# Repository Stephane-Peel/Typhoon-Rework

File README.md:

# Typhoon
Clouds variant

Fork to share production files used to make mine.

- Frontpanel rework to my taste.
- Kicad conversion from Diptrace
- 3D CAD : Fusion 360 & STL
- Original Fuzzy BOM reference completed

Beware : 
--------
The current files where used for my build.
It should be ok, but please double check everything to make your own module ;)

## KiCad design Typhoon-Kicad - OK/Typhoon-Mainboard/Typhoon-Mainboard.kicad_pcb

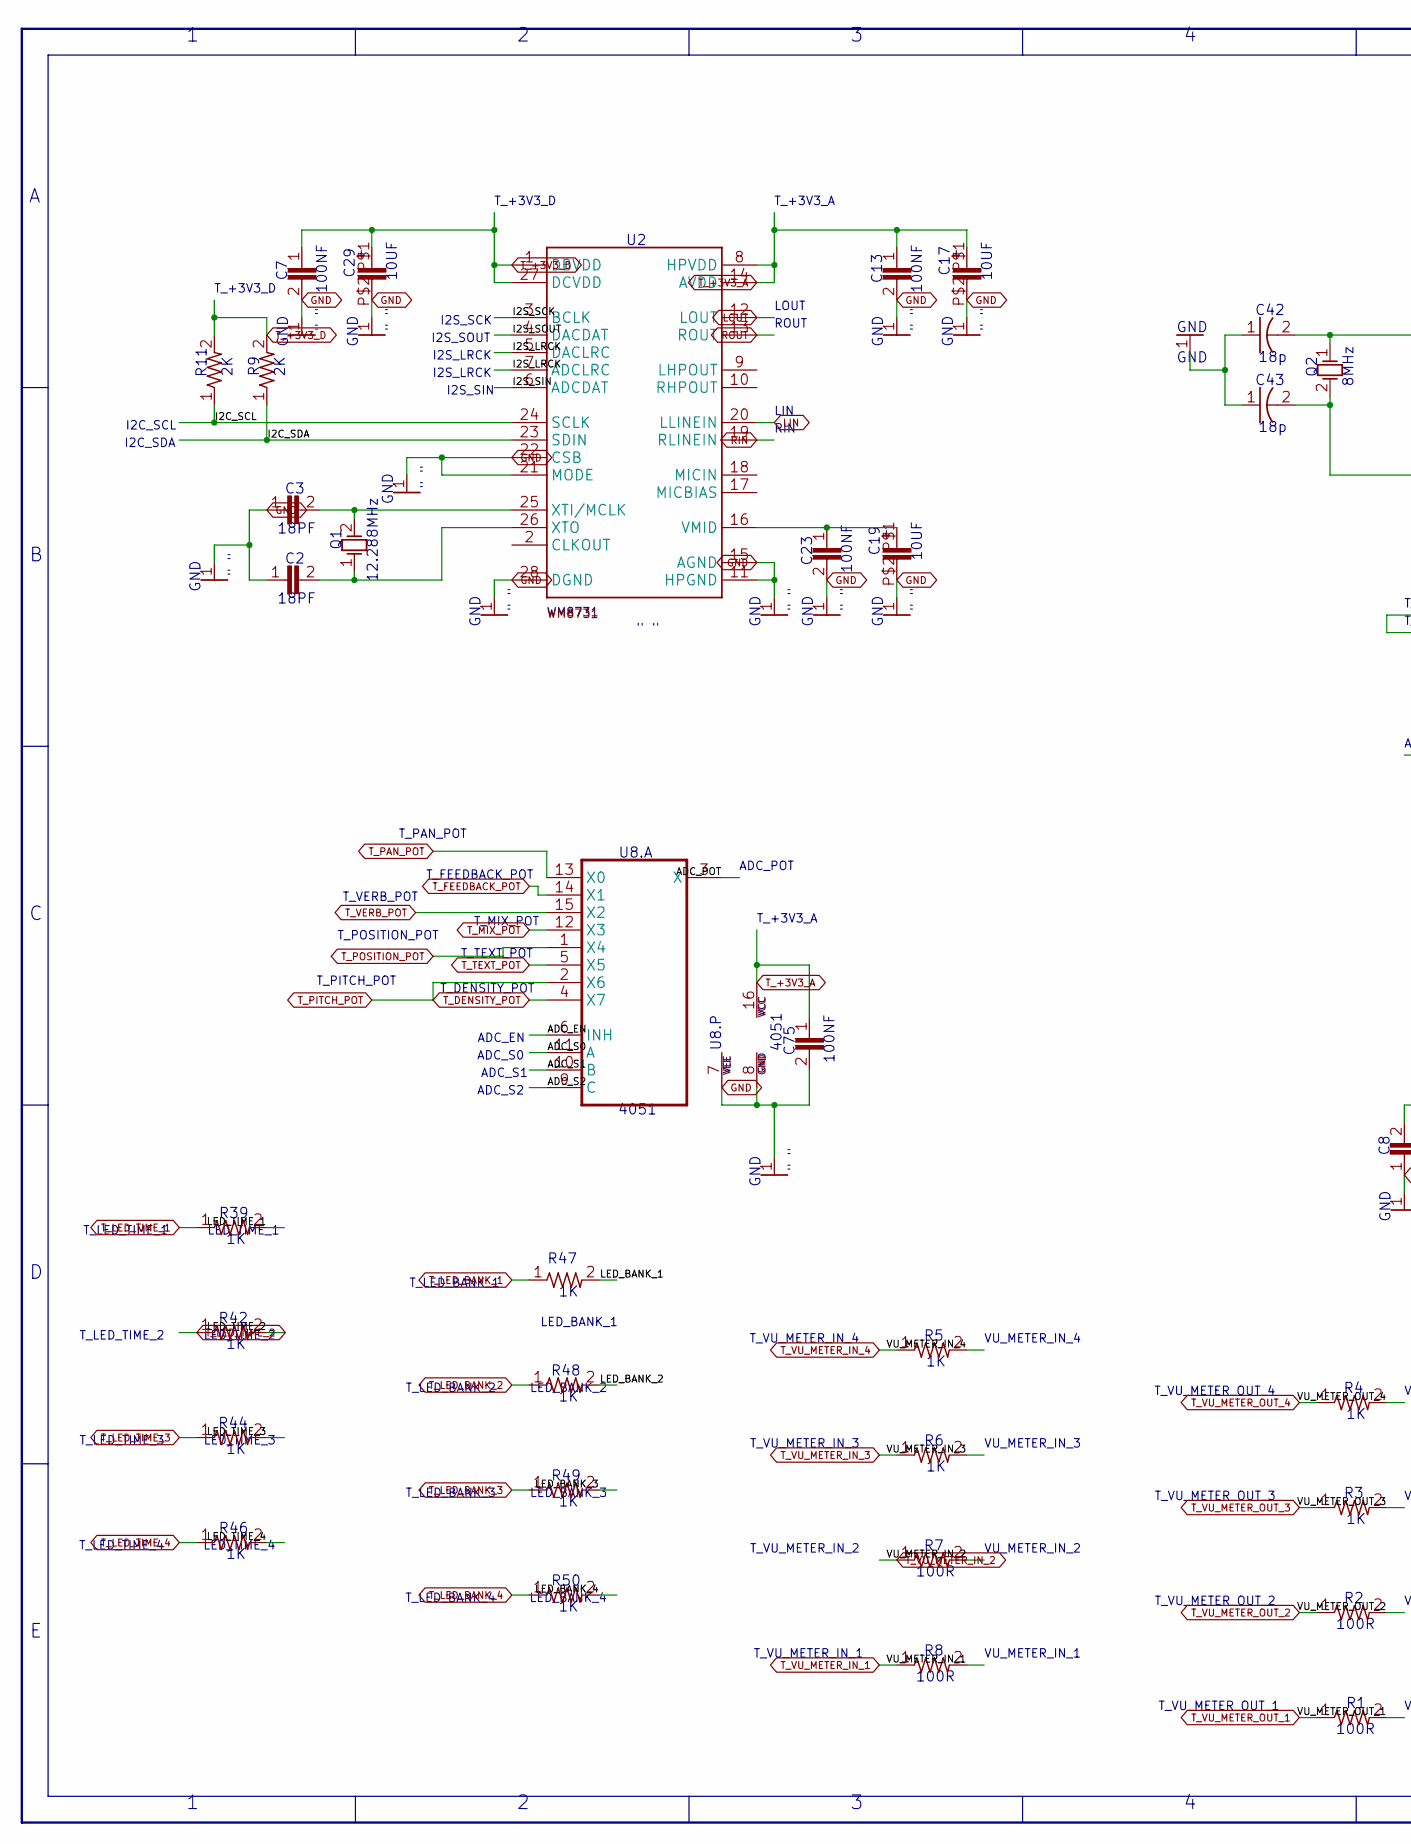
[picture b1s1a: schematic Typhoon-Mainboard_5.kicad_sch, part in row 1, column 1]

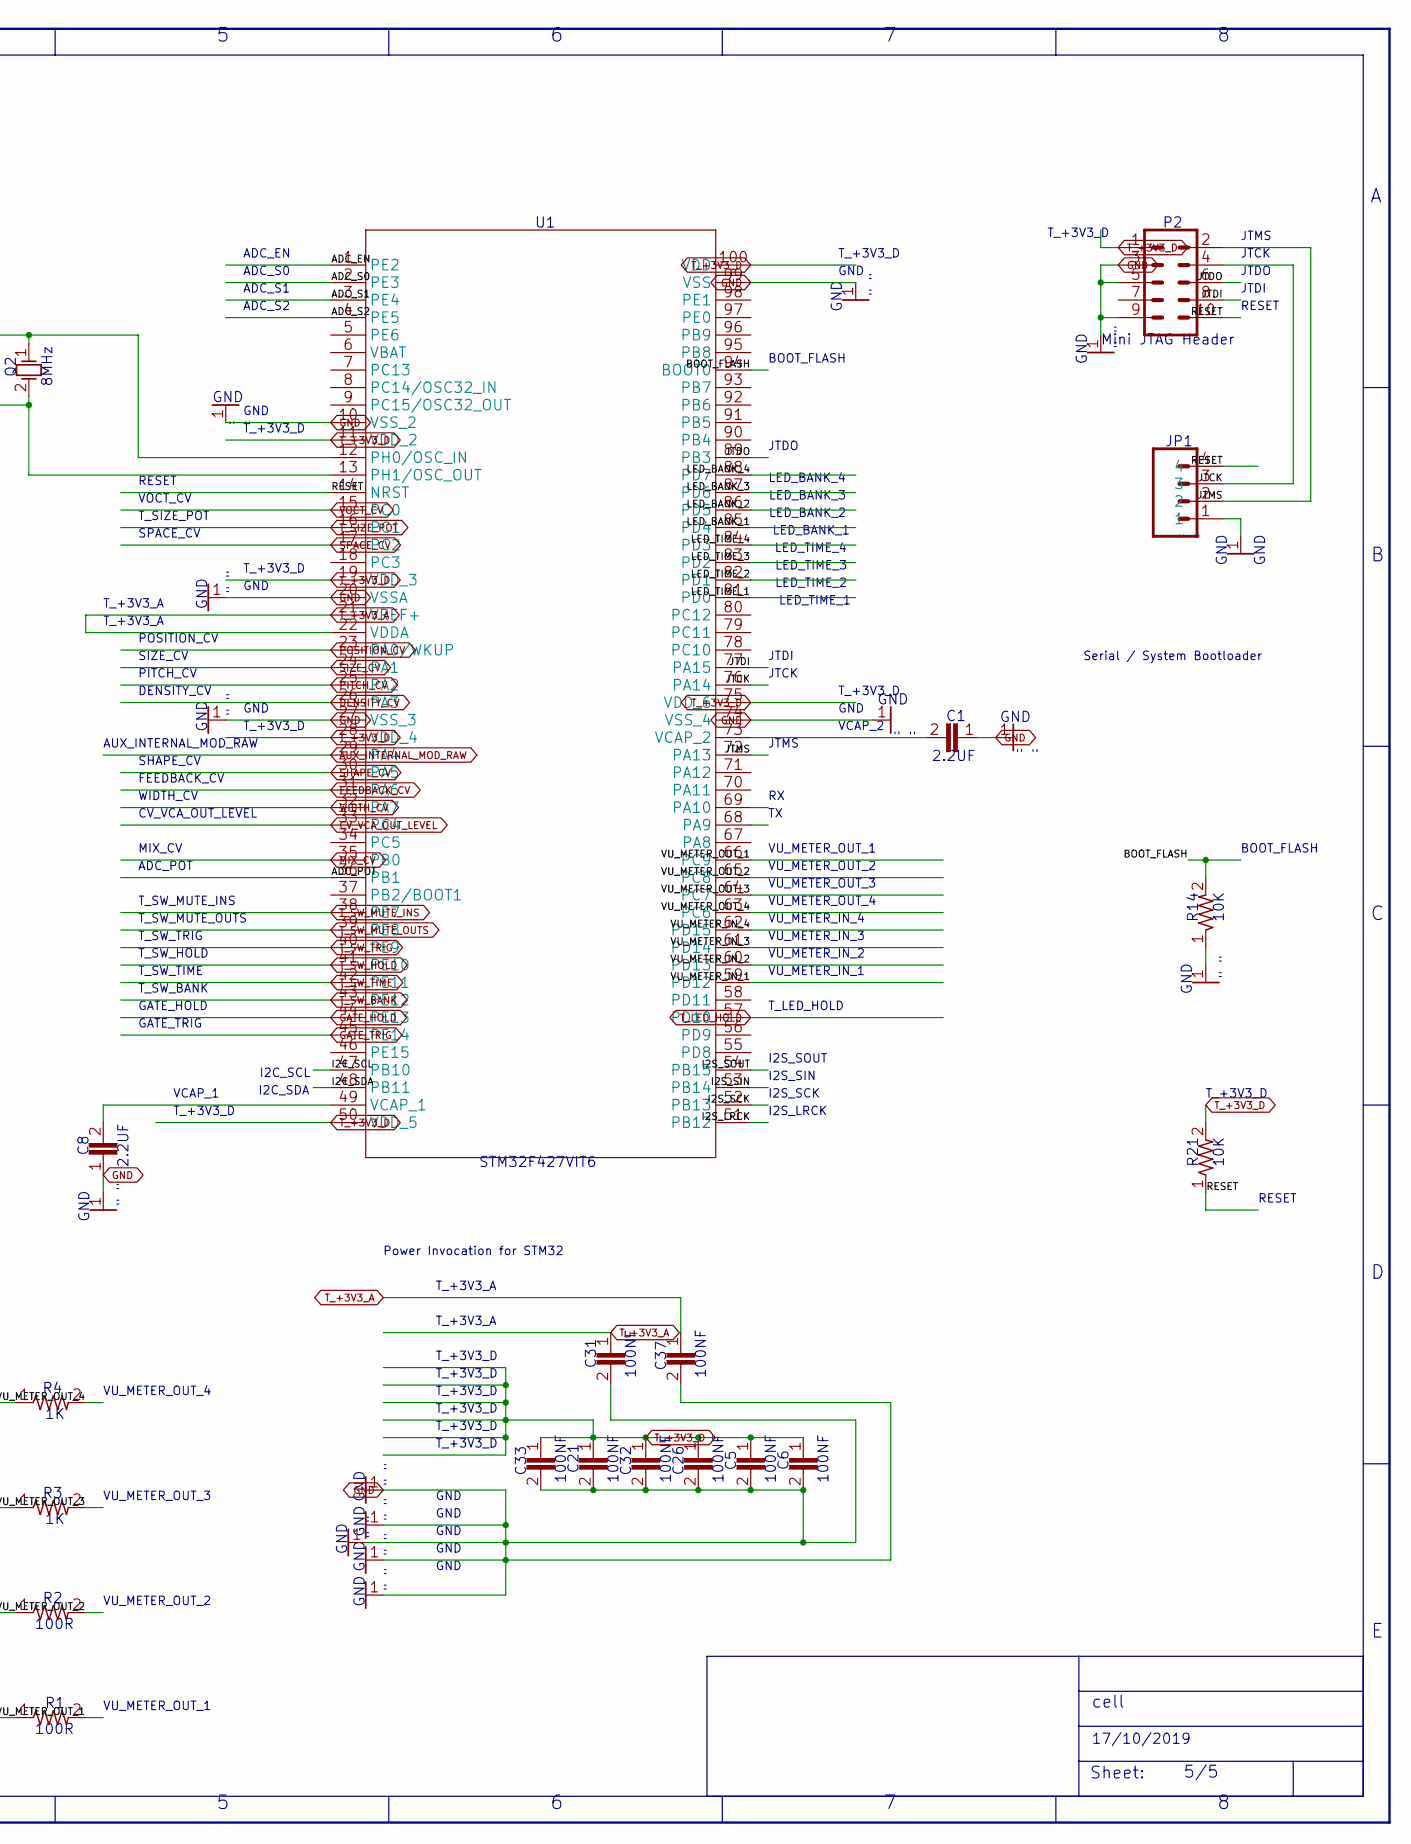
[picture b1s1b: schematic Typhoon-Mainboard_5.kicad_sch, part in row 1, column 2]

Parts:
C1, C8: 2.2UF; CAP_0603
C2, C3: 18PF; CAP_0603
C5, C6, C7, C13, C21, C23, C26, C31, C32, C33, C37, C75: 100NF; CAP_0603
C17, C19, C29: 10UF; EC-4X7
C42, C43: 18p; CAP_0603
JP1: M04PTH; 1X04
P2: Mini JTAG Header; 2X5-1.27
Q1: 12.288MHz; TSC_7A_CRYSTAL
Q2: 8MHz; TSC_7A_CRYSTAL
R1, R2, R7, R8: 100R; RES_0603
R3, R4, R5, R6, R39, R42, R44, R46, R47, R48, R49, R50: 1K; RES_0603
R9, R11: 2K; RES_0603
R14, R21: 10K; RES_0603
U1: STM32F427VIT6; LQFP100-14X14MM
U2: WM8731; SSOP-28
U8: 4051; SO-16

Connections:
ADC_EN: U1.1 (PE2), U8.6 (INH)
ADC_POT: U1.36 (PB1), U8.3 (X)
ADC_S0: U1.2 (PE3), U8.11 (A)
ADC_S1: U1.3 (PE4), U8.10 (B)
ADC_S2: U1.4 (PE5), U8.9 (C)
AUX_INTERNAL_MOD_RAW: U1.29 (PA4); also elsewhere on the board
BOOT_FLASH: R14.2, U1.94 (BOOT0)
CV_VCA_OUT_LEVEL: U1.33 (PC4); also elsewhere on the board
DENSITY_CV: U1.26 (PA3); also elsewhere on the board
FEEDBACK_CV: U1.31 (PA6); also elsewhere on the board
GATE_HOLD: U1.44 (PE13); also elsewhere on the board
GATE_TRIG: U1.45 (PE14); also elsewhere on the board
I2C_SCL: R11.1, U1.47 (PB10), U2.24 (SCLK)
I2C_SDA: R9.1, U1.48 (PB11), U2.23 (SDIN)
I2S_LRCK: U1.51 (PB12), U2.5 (DACLRC), U2.7 (ADCLRC)
I2S_SCK: U1.52 (PB13), U2.3 (BCLK)
I2S_SIN: U1.53 (PB14), U2.6 (ADCDAT)
I2S_SOUT: U1.54 (PB15), U2.4 (DACDAT)
JTCK: JP1.3, P2.4, U1.76 (PA14)
JTDI: P2.8, U1.77 (PA15)
JTDO: P2.6, U1.89 (PB3)
JTMS: JP1.2, P2.2, U1.72 (PA13)
LED_BANK_1: R47.2, U1.85 (PD4)
LED_BANK_2: R48.2, U1.86 (PD5)
LED_BANK_3: R49.2, U1.87 (PD6)
LED_BANK_4: R50.2, U1.88 (PD7)
LED_TIME_1: R39.2, U1.81 (PD0)
LED_TIME_2: R42.2, U1.82 (PD1)
LED_TIME_3: R44.2, U1.83 (PD2)
LED_TIME_4: R46.2, U1.84 (PD3)
LIN: U2.20 (LLINEIN); also elsewhere on the board
LOUT: U2.12 (LOUT); also elsewhere on the board
MIX_CV: U1.35 (PB0); also elsewhere on the board
unnamed: C19.P$1 (POS), C23.1, U2.16 (VMID)
unnamed: C2.2, Q1.1 (OSC1), U2.26 (XTO)
unnamed: C3.2, Q1.2 (OSC2), U2.25 (XTI/MCLK)
unnamed: C42.2, Q2.1 (OSC1), U1.12 (PH0/OSC_IN)
Net_84: C43.2, Q2.2 (OSC2), U1.13 (PH1/OSC_OUT)
PITCH_CV: U1.25 (PA2); also elsewhere on the board
POSITION_CV: U1.23 (PA0/WKUP); also elsewhere on the board
RESET: JP1.4, P2.10, R21.1, U1.14 (NRST)
RIN: U2.19 (RLINEIN); also elsewhere on the board
ROUT: U2.13 (ROUT); also elsewhere on the board
SHAPE_CV: U1.30 (PA5); also elsewhere on the board
SIZE_CV: U1.24 (PA1); also elsewhere on the board
SPACE_CV: U1.17 (PC2); also elsewhere on the board
T_+3V3_A: C13.1, C17.P$1 (POS), C31.1, C37.1, C75.1, U1.21 (VREF+), U1.22 (VDDA), U2.8 (HPVDD), U2.14 (AVDD), U8.16 (VCC); also elsewhere on the board
T_DENSITY_POT: U8.4 (X7); also elsewhere on the board
T_FEEDBACK_POT: U8.14 (X1); also elsewhere on the board
T_LED_BANK_1: R47.1; also elsewhere on the board
T_LED_BANK_2: R48.1; also elsewhere on the board
T_LED_BANK_3: R49.1; also elsewhere on the board
T_LED_BANK_4: R50.1; also elsewhere on the board
T_LED_HOLD: U1.57 (PD10); also elsewhere on the board
T_LED_TIME_1: R39.1; also elsewhere on the board
T_LED_TIME_2: R42.1; also elsewhere on the board
T_LED_TIME_3: R44.1; also elsewhere on the board
T_LED_TIME_4: R46.1; also elsewhere on the board
T_MIX_POT: U8.12 (X3); also elsewhere on the board
T_PAN_POT: U8.13 (X0); also elsewhere on the board
T_PITCH_POT: U8.2 (X6); also elsewhere on the board
T_POSITION_POT: U8.1 (X4); also elsewhere on the board
T_SIZE_POT: U1.16 (PC1); also elsewhere on the board
T_SW_HOLD: U1.41 (PE10); also elsewhere on the board
T_SW_MUTE_OUTS: U1.39 (PE8); also elsewhere on the board
T_SW_TIME: U1.42 (PE11); also elsewhere on the board
T_SW_TRIG: U1.40 (PE9); also elsewhere on the board
T_TEXT_POT: U8.5 (X5); also elsewhere on the board
T_VERB_POT: U8.15 (X2); also elsewhere on the board
T_VU_METER_IN_1: R8.1; also elsewhere on the board
T_VU_METER_IN_2: R7.1; also elsewhere on the board
T_VU_METER_IN_3: R6.1; also elsewhere on the board
T_VU_METER_IN_4: R5.1; also elsewhere on the board
T_VU_METER_OUT_1: R1.1; also elsewhere on the board
T_VU_METER_OUT_2: R2.1; also elsewhere on the board
T_VU_METER_OUT_3: R3.1; also elsewhere on the board
T_VU_METER_OUT_4: R4.1; also elsewhere on the board
VCAP_1: C8.2, U1.49 (VCAP_1)
VCAP_2: C1.2, U1.73 (VCAP_2)
VOCT_CV: U1.15 (PC0); also elsewhere on the board
VU_METER_IN_1: R8.2, U1.59 (PD12)
VU_METER_IN_2: R7.2, U1.60 (PD13)
VU_METER_IN_3: R6.2, U1.61 (PD14)
VU_METER_IN_4: R5.2, U1.62 (PD15)
VU_METER_OUT_1: R1.2, U1.66 (PC9)
VU_METER_OUT_2: R2.2, U1.65 (PC8)
VU_METER_OUT_3: R3.2, U1.64 (PC7)
VU_METER_OUT_4: R4.2, U1.63 (PC6)
WIDTH_CV: U1.32 (PA7); also elsewhere on the board

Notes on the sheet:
C13
10K
JTDO
I2S_SOUT
GND
LED_TIME_1
R14
100NF
VU_METER_OUT_4
LED_BANK_2
JTMS
T_VU_METER_OUT_2
" "
T_+3V3_D
12.288MHz
18PF
WM8731
T_SW_TRIG
BOOT_FLASH
CV_VCA_OUT_LEVEL
100R
T_LED_TIME_2
T_+3V3_A
U8.A
ADC_S2
LED_BANK_4
LED_TIME_4
ROUT
JTCK
LED_TIME_2
LED_BANK_3
T_LED_TIME_1
C75
JTDI
T_SW_MUTE_INS
C42
VU_METER_OUT_2
I2S_LRCK
LED_BANK_1
I2C_SCL

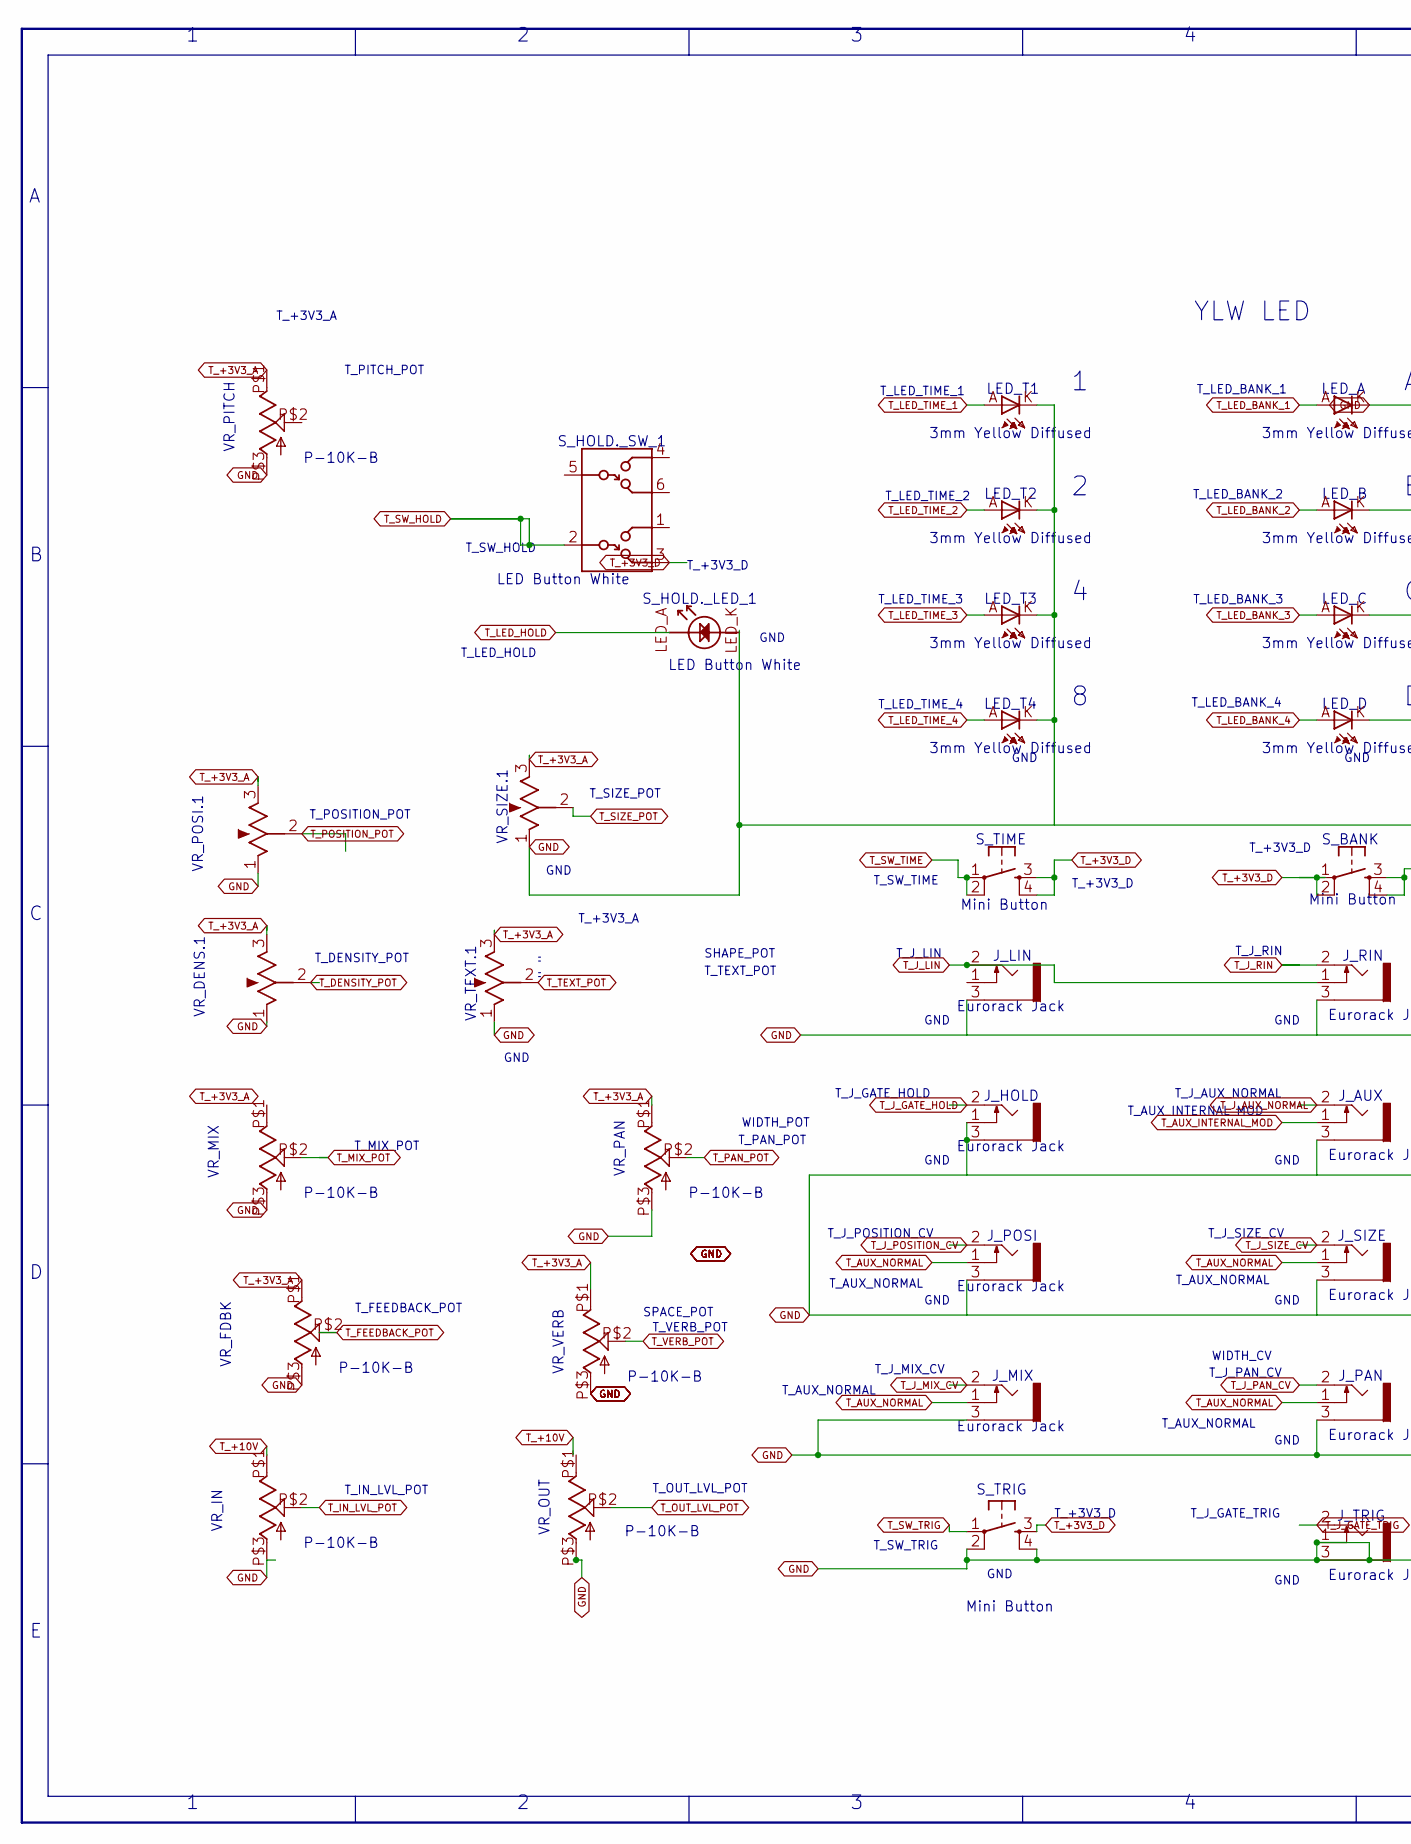
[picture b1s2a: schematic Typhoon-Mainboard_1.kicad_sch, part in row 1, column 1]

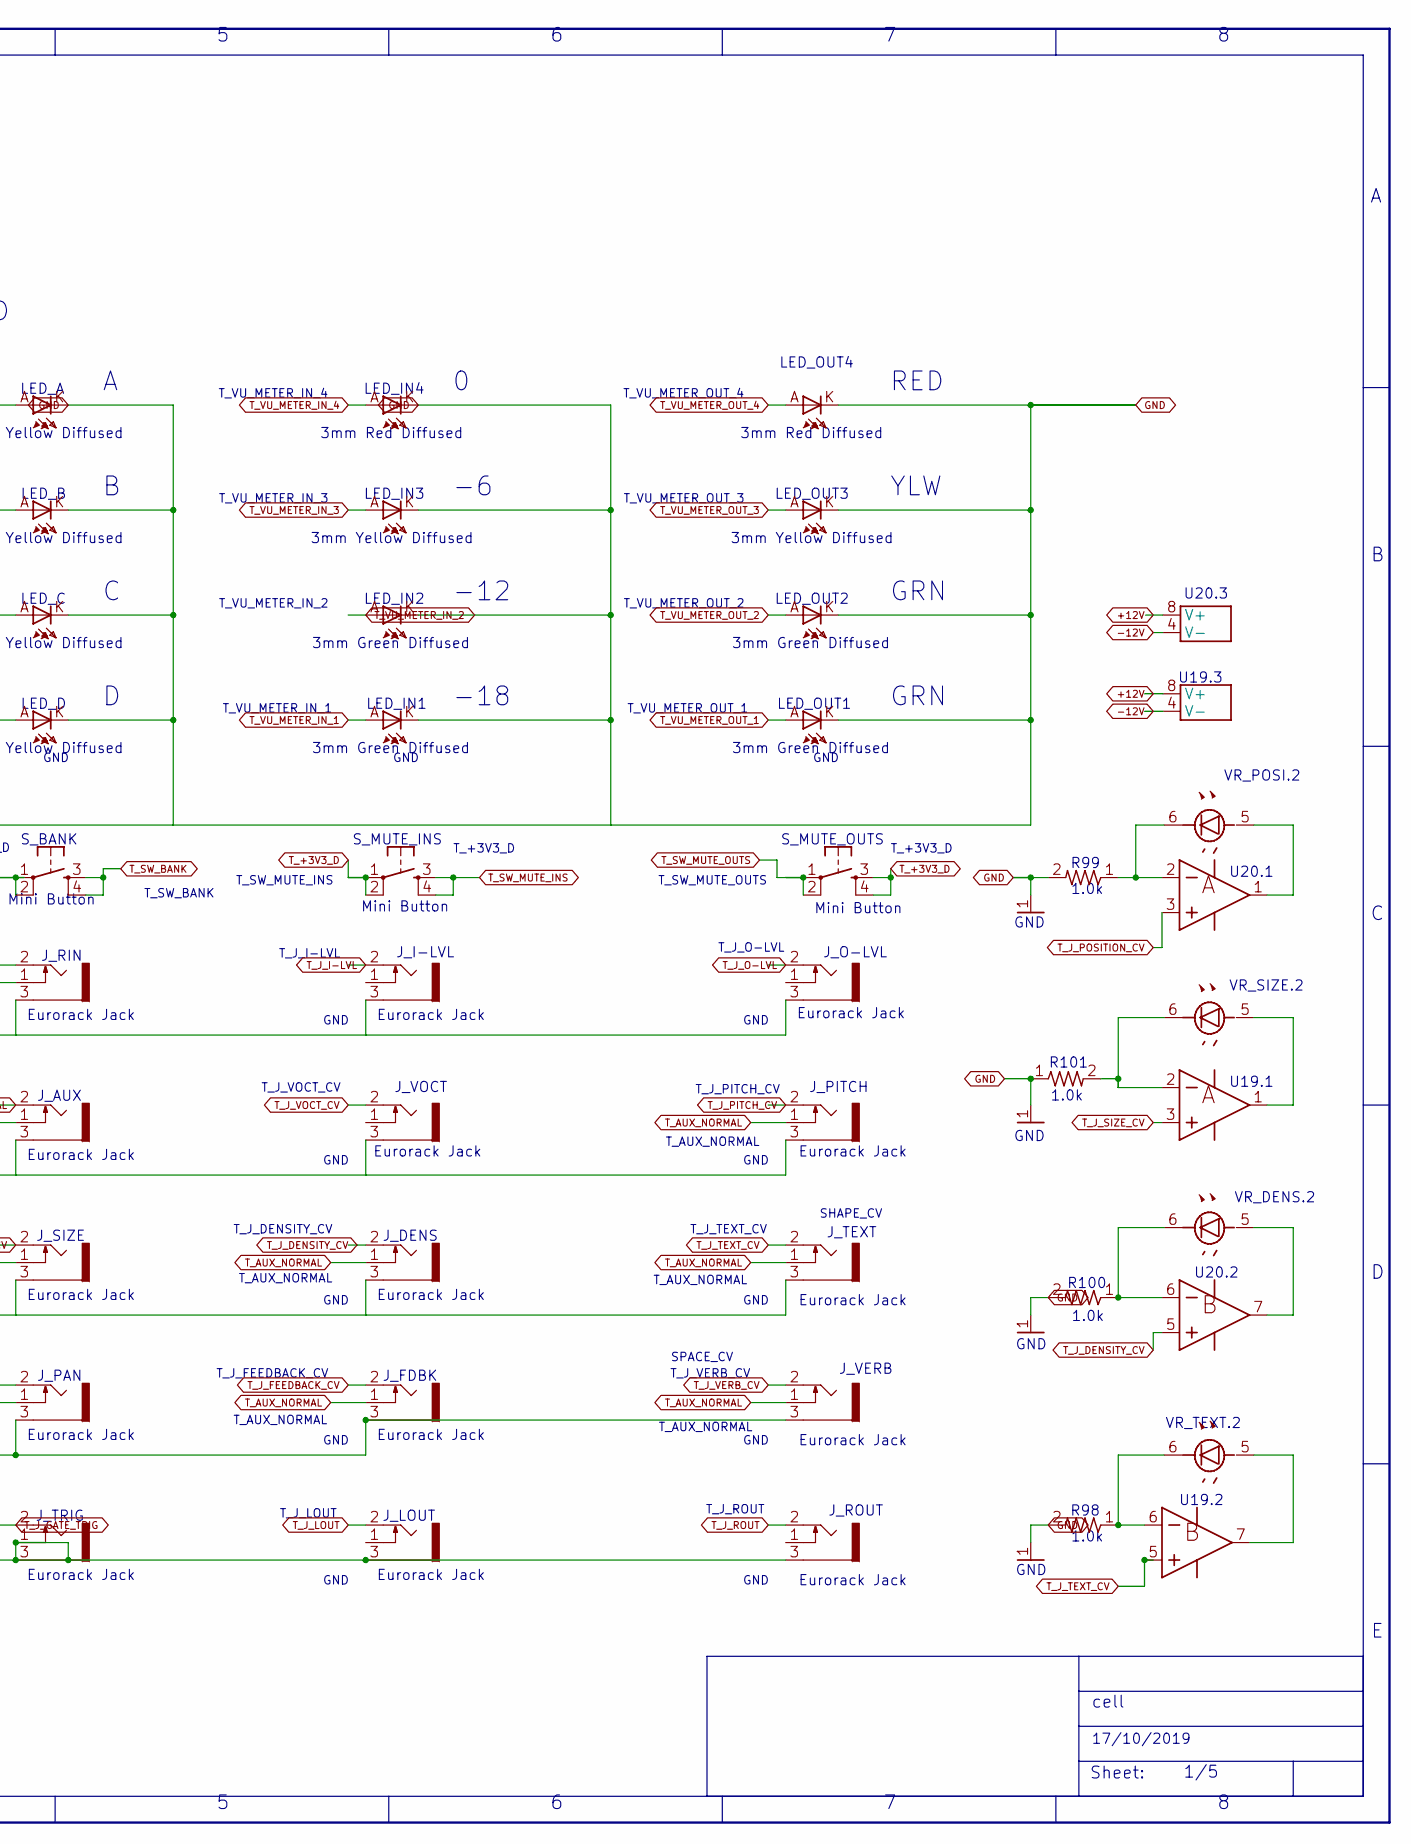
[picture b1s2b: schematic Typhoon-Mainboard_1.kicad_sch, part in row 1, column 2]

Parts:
J_AUX0: Eurorack Jack; THONKICONN
J_DENS0: Eurorack Jack; THONKICONN
J_FDBK0: Eurorack Jack; THONKICONN
J_HOLD0: Eurorack Jack; THONKICONN
J_I-LVL0: Eurorack Jack; THONKICONN
J_LIN0: Eurorack Jack; THONKICONN
J_LOUT0: Eurorack Jack; THONKICONN
J_MIX0: Eurorack Jack; THONKICONN
J_O-LVL0: Eurorack Jack; THONKICONN
J_PAN0: Eurorack Jack; THONKICONN
J_PITCH0: Eurorack Jack; THONKICONN
J_POSI0: Eurorack Jack; THONKICONN
J_RIN0: Eurorack Jack; THONKICONN
J_ROUT0: Eurorack Jack; THONKICONN
J_SIZE0: Eurorack Jack; THONKICONN
J_TEXT0: Eurorack Jack; THONKICONN
J_TRIG0: Eurorack Jack; THONKICONN
J_VERB0: Eurorack Jack; THONKICONN
J_VOCT0: Eurorack Jack; THONKICONN
LED_A0: 3mm Yellow Diffused; LED_SILK
LED_B0: 3mm Yellow Diffused; LED_SILK
LED_C0: 3mm Yellow Diffused; LED_SILK
LED_D0: 3mm Yellow Diffused; LED_SILK
LED_IN1, LED_IN2: 3mm Green Diffused; LED_SILK
LED_IN3: 3mm Yellow Diffused; LED_SILK
LED_IN4: 3mm Red Diffused; LED_SILK
LED_OUT1, LED_OUT2: 3mm Green Diffused; LED_SILK
LED_OUT3: 3mm Yellow Diffused; LED_SILK
LED_OUT4: 3mm Red Diffused; LED_SILK
LED_T1, LED_T2, LED_T3, LED_T4: 3mm Yellow Diffused; LED_SILK
R98, R99, R100, R101: 1.0k; RES_0603
S_BANK0: Mini Button; TACTILE-PTH_SILK
S_HOLD0: LED Button White; LED_BUTTON_SILK
S_MUTE_INS0: Mini Button; TACTILE-PTH_SILK
S_MUTE_OUTS0: Mini Button; TACTILE-PTH_SILK
S_TIME0: Mini Button; TACTILE-PTH_SILK
S_TRIG0: Mini Button; TACTILE-PTH_SILK
U19, U20: TLV2172; TSSOP-8
VR_DENS0: BOURNS_PTL_LED_SLIDE_POT; BOURNS_PTL_30MM
VR_FDBK0: P-10K-B; ALPS_POT_VERTICAL_PS
VR_IN0: P-10K-B; ALPS_POT_VERTICAL_PS
VR_MIX0: P-10K-B; ALPS_POT_VERTICAL_PS
VR_OUT0: P-10K-B; ALPS_POT_VERTICAL_PS
VR_PAN0: P-10K-B; ALPS_POT_VERTICAL_PS
VR_PITCH0: P-10K-B; ALPS_POT_VERTICAL_PS
VR_POSI0: BOURNS_PTL_LED_SLIDE_POT; BOURNS_PTL_30MM
VR_SIZE0: BOURNS_PTL_LED_SLIDE_POT; BOURNS_PTL_30MM
VR_TEXT0: BOURNS_PTL_LED_SLIDE_POT; BOURNS_PTL_30MM
VR_VERB0: P-10K-B; ALPS_POT_VERTICAL_PS

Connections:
+12V: U19.8 (V+), U20.8 (V+); also elsewhere on the board
-12V: U19.4 (V-), U20.4 (V-); also elsewhere on the board
Net_1: R99.1, U20.2 (IN-), VR_POSI0.6 (gnd@2)
Net_110: R100.1, U20.6 (IN-), VR_DENS0.6 (gnd@2)
Net_116: R98.1, U19.6 (IN-), VR_TEXT0.6 (gnd@2)
Net_177: U20.1 (OUT), VR_POSI0.5 (gnd@1)
Net_178: U19.1 (OUT), VR_SIZE0.5 (gnd@1)
Net_182: U20.7 (OUT), VR_DENS0.5 (gnd@1)
Net_183: U19.7 (OUT), VR_TEXT0.5 (gnd@1)
T_+3V3_A: VR_DENS0.3 (CW), VR_FDBK0.P$1 (3), VR_MIX0.P$1 (3), VR_PAN0.P$1 (3), VR_PITCH0.P$1 (3), VR_POSI0.3 (CW), VR_SIZE0.3 (CW), VR_TEXT0.3 (CW), VR_VERB0.P$1 (3); also elsewhere on the board
T_+10V: VR_IN0.P$1 (3), VR_OUT0.P$1 (3); also elsewhere on the board
T_AUX_INTERNAL_MOD: J_AUX0.1 (NORM); also elsewhere on the board
T_AUX_NORMAL: J_DENS0.1 (NORM), J_FDBK0.1 (NORM), J_MIX0.1 (NORM), J_PAN0.1 (NORM), J_PITCH0.1 (NORM), J_POSI0.1 (NORM), J_SIZE0.1 (NORM), J_TEXT0.1 (NORM), J_VERB0.1 (NORM); also elsewhere on the board
T_DENSITY_POT: VR_DENS0.2 (W); also elsewhere on the board
T_FEEDBACK_POT: VR_FDBK0.P$2 (2); also elsewhere on the board
T_IN_LVL_POT: VR_IN0.P$2 (2); also elsewhere on the board
T_J_AUX_NORMAL: J_AUX0.2 (TIP); also elsewhere on the board
T_J_DENSITY_CV: J_DENS0.2 (TIP), U20.5 (IN+); also elsewhere on the board
T_J_FEEDBACK_CV: J_FDBK0.2 (TIP); also elsewhere on the board
T_J_GATE_HOLD: J_HOLD0.2 (TIP); also elsewhere on the board
T_J_GATE_TRIG: J_TRIG0.2 (TIP); also elsewhere on the board
T_J_I-LVL: J_I-LVL0.2 (TIP); also elsewhere on the board
T_J_LIN: J_LIN0.2 (TIP), J_RIN0.1 (NORM); also elsewhere on the board
T_J_LOUT: J_LOUT0.2 (TIP); also elsewhere on the board
T_J_MIX_CV: J_MIX0.2 (TIP); also elsewhere on the board
T_J_O-LVL: J_O-LVL0.2 (TIP); also elsewhere on the board
T_J_PAN_CV: J_PAN0.2 (TIP); also elsewhere on the board
T_J_PITCH_CV: J_PITCH0.2 (TIP); also elsewhere on the board
T_J_POSITION_CV: J_POSI0.2 (TIP), U20.3 (IN+); also elsewhere on the board
T_J_RIN: J_RIN0.2 (TIP); also elsewhere on the board
T_J_ROUT: J_ROUT0.2 (TIP); also elsewhere on the board
T_J_SIZE_CV: J_SIZE0.2 (TIP), U19.3 (IN+); also elsewhere on the board
T_J_TEXT_CV: J_TEXT0.2 (TIP), U19.5 (IN+); also elsewhere on the board
T_J_VERB_CV: J_VERB0.2 (TIP); also elsewhere on the board
T_J_VOCT_CV: J_VOCT0.2 (TIP); also elsewhere on the board
T_LED_BANK_1: LED_A0.A; also elsewhere on the board
T_LED_BANK_2: LED_B0.A; also elsewhere on the board
T_LED_BANK_3: LED_C0.A; also elsewhere on the board
T_LED_BANK_4: LED_D0.A; also elsewhere on the board
T_LED_HOLD: S_HOLD0.LED_A; also elsewhere on the board
T_LED_TIME_1: LED_T1.A; also elsewhere on the board
T_LED_TIME_2: LED_T2.A; also elsewhere on the board
T_LED_TIME_3: LED_T3.A; also elsewhere on the board
T_LED_TIME_4: LED_T4.A; also elsewhere on the board
T_MIX_POT: VR_MIX0.P$2 (2); also elsewhere on the board
T_OUT_LVL_POT: VR_OUT0.P$2 (2); also elsewhere on the board
T_PAN_POT: VR_PAN0.P$2 (2); also elsewhere on the board
T_PITCH_POT: VR_PITCH0.P$2 (2); also elsewhere on the board
T_POSITION_POT: VR_POSI0.2 (W); also elsewhere on the board
T_SIZE_POT: VR_SIZE0.2 (W); also elsewhere on the board
T_SW_HOLD: S_HOLD0.2; also elsewhere on the board
T_SW_MUTE_OUTS: S_MUTE_OUTS0.1, S_MUTE_OUTS0.2; also elsewhere on the board
T_SW_TIME: S_TIME0.1, S_TIME0.2; also elsewhere on the board
T_SW_TRIG: S_TRIG0.1; also elsewhere on the board
T_TEXT_POT: VR_TEXT0.2 (W); also elsewhere on the board
T_VERB_POT: VR_VERB0.P$2 (2); also elsewhere on the board
T_VU_METER_IN_1: LED_IN1.A; also elsewhere on the board
T_VU_METER_IN_2: LED_IN2.A; also elsewhere on the board
T_VU_METER_IN_3: LED_IN3.A; also elsewhere on the board
T_VU_METER_IN_4: LED_IN4.A; also elsewhere on the board
T_VU_METER_OUT_1: LED_OUT1.A; also elsewhere on the board
T_VU_METER_OUT_2: LED_OUT2.A; also elsewhere on the board
T_VU_METER_OUT_3: LED_OUT3.A; also elsewhere on the board
T_VU_METER_OUT_4: LED_OUT4.A; also elsewhere on the board

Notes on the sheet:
T_+3V3_A
GND
S_TIME
T_+3V3_D
Eurorack Jack
VR_TEXT.1
LED_OUT3
LED_IN3
T_J_GATE_TRIG
T_J_VERB_CV
T_VU_METER_IN_4
T_VU_METER_OUT_2
T_IN_LVL_POT
VR_PAN
WIDTH_POT
J_I-LVL
P-10K-B
1.0k
J_LIN
T_PITCH_POT
T_SW_HOLD
T_POSITION_POT
T_SW_TRIG
3mm Yellow Diffused
SHAPE_POT
T_LED_TIME_2
J_TRIG
J_AUX
3mm Red Diffused
S_MUTE_INS
T_SW_MUTE_OUTS
WIDTH_CV
T_J_POSITION_CV
T_AUX_NORMAL
VR_VERB
LED_IN1
Mini Button
LED_OUT2
VR_MIX
J_PITCH

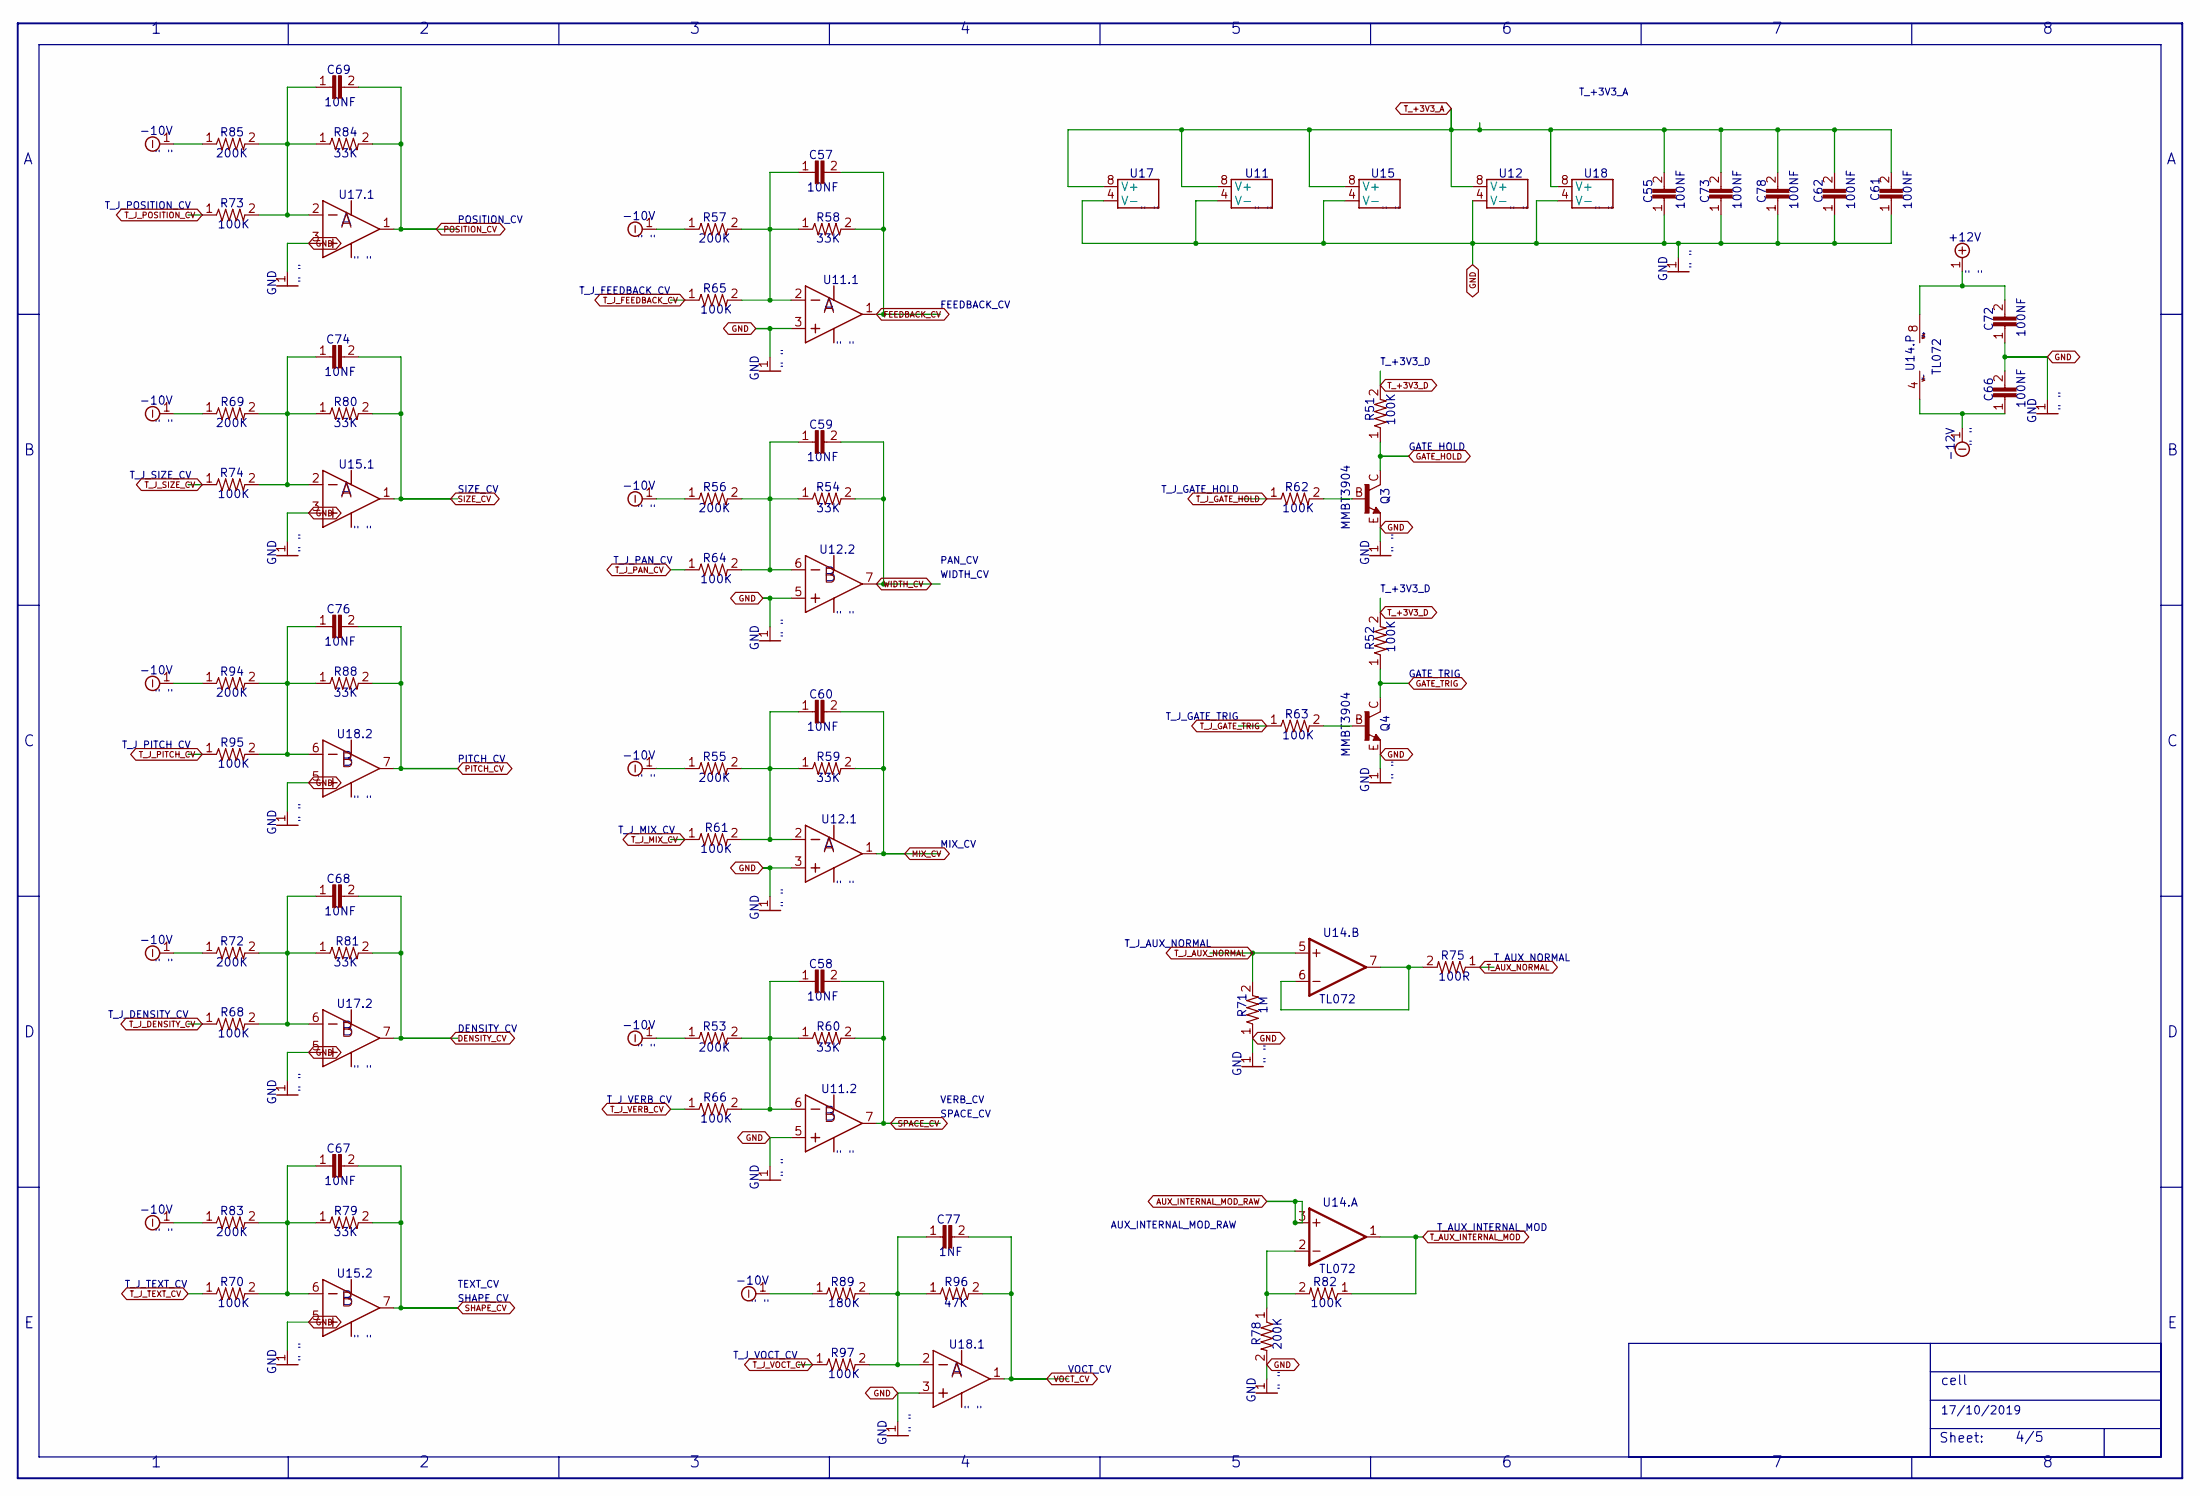
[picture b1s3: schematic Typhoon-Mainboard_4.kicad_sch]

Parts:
C55, C61, C62, C66, C72, C73, C78: 100NF; CAP_0603
C57, C58, C59, C60, C67, C68, C69, C74, C76: 10NF; CAP_0603
C77: 1NF; CAP_0603
Q3, Q4: MMBT3904; SOT23-BEC
R51, R52, R61, R62, R63, R64, R65, R66, R68, R70, R73, R74, R82, R95, R97: 100K; RES_0603
R53, R55, R56, R57, R69, R72, R78, R83, R85, R94: 200K; RES_0603
R54, R58, R59, R60, R79, R80, R81, R84, R88: 33K; RES_0603
R71: 1M; RES_0603
R75: 100R; RES_0603
R89: 180K; RES_0603
R96: 47K; RES_0603
U11, U12, U15, U17, U18: MCP6002; SOIC-8_150MIL
U14: TL072; SO-8

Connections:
+12V: C72.2, U14.8 (V+); also elsewhere on the board
-10V: R53.1, R55.1, R56.1, R57.1, R69.1, R72.1, R83.1, R85.1, R89.1, R94.1; also elsewhere on the board
-12V: C66.1, U14.4 (V-); also elsewhere on the board
AUX_INTERNAL_MOD_RAW: U14.3 (+IN); also elsewhere on the board
DENSITY_CV: C68.2, R81.2, U17.7 (OUT); also elsewhere on the board
FEEDBACK_CV: C57.2, R58.2, U11.1 (OUT); also elsewhere on the board
GATE_HOLD: Q3.C, R51.1; also elsewhere on the board
GATE_TRIG: Q4.C, R52.1; also elsewhere on the board
MIX_CV: C60.2, R59.2, U12.1 (OUT); also elsewhere on the board
unnamed: C74.1, R69.2, R74.2, R80.1, U15.2 (IN-)
unnamed: C76.1, R88.1, R94.2, R95.2, U18.6 (IN-)
unnamed: C68.1, R68.2, R72.2, R81.1, U17.6 (IN-)
unnamed: C57.1, R57.2, R58.1, R65.2, U11.2 (IN-)
unnamed: C59.1, R54.1, R56.2, R64.2, U12.6 (IN-)
unnamed: C60.1, R55.2, R59.1, R61.2, U12.2 (IN-)
unnamed: C58.1, R53.2, R60.1, R66.2, U11.6 (IN-)
unnamed: C67.1, R70.2, R79.1, R83.2, U15.6 (IN-)
unnamed: R75.2, U14.6 (-IN), U14.7 (OUT)
unnamed: Q3.B, R62.2
unnamed: C77.1, R89.2, R96.1, R97.2, U18.2 (IN-)
unnamed: Q4.B, R63.2
unnamed: C69.1, R73.2, R84.1, R85.2, U17.2 (IN-)
unnamed: R78.1, R82.2, U14.2 (-IN)
PITCH_CV: C76.2, R88.2, U18.7 (OUT); also elsewhere on the board
POSITION_CV: C69.2, R84.2, U17.1 (OUT); also elsewhere on the board
SHAPE_CV: C67.2, R79.2, U15.7 (OUT); also elsewhere on the board
SIZE_CV: C74.2, R80.2, U15.1 (OUT); also elsewhere on the board
SPACE_CV: C58.2, R60.2, U11.7 (OUT); also elsewhere on the board
T_+3V3_A: C55.2, C61.2, C62.2, C73.2, C78.2, U11.8 (V+), U12.8 (V+), U15.8 (V+), U17.8 (V+), U18.8 (V+); also elsewhere on the board
T_AUX_INTERNAL_MOD: R82.1, U14.1 (OUT); also elsewhere on the board
T_AUX_NORMAL: R75.1; also elsewhere on the board
T_J_AUX_NORMAL: R71.2, U14.5 (+IN); also elsewhere on the board
T_J_DENSITY_CV: R68.1; also elsewhere on the board
T_J_FEEDBACK_CV: R65.1; also elsewhere on the board
T_J_GATE_HOLD: R62.1; also elsewhere on the board
T_J_GATE_TRIG: R63.1; also elsewhere on the board
T_J_MIX_CV: R61.1; also elsewhere on the board
T_J_PAN_CV: R64.1; also elsewhere on the board
T_J_PITCH_CV: R95.1; also elsewhere on the board
T_J_POSITION_CV: R73.1; also elsewhere on the board
T_J_SIZE_CV: R74.1; also elsewhere on the board
T_J_TEXT_CV: R70.1; also elsewhere on the board
T_J_VERB_CV: R66.1; also elsewhere on the board
T_J_VOCT_CV: R97.1; also elsewhere on the board
VOCT_CV: C77.2, R96.2, U18.1 (OUT); also elsewhere on the board
WIDTH_CV: C59.2, R54.2, U12.7 (OUT); also elsewhere on the board

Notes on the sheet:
R59
100K
GND
" "
C60
T_AUX_NORMAL
U14.A
R65
+12V
GATE_TRIG
-10V
T_J_FEEDBACK_CV
C55
C72
10NF
TEXT_CV
T_AUX_INTERNAL_MOD
VERB_CV
C78
33K
PAN_CV
T_J_PITCH_CV
T_J_PAN_CV
U14.P
R66
100NF
C57
R80
U17.2
C76
R88
MMBT3904
U18
200K
R83
FEEDBACK_CV
R55
R85
R73
1NF

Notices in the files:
Typhoon-Kicad - OK/Typhoon-Mainboard/Typhoon-Mainboard.kicad_pcb:
E. Gillet CC BY-SA 3.0
